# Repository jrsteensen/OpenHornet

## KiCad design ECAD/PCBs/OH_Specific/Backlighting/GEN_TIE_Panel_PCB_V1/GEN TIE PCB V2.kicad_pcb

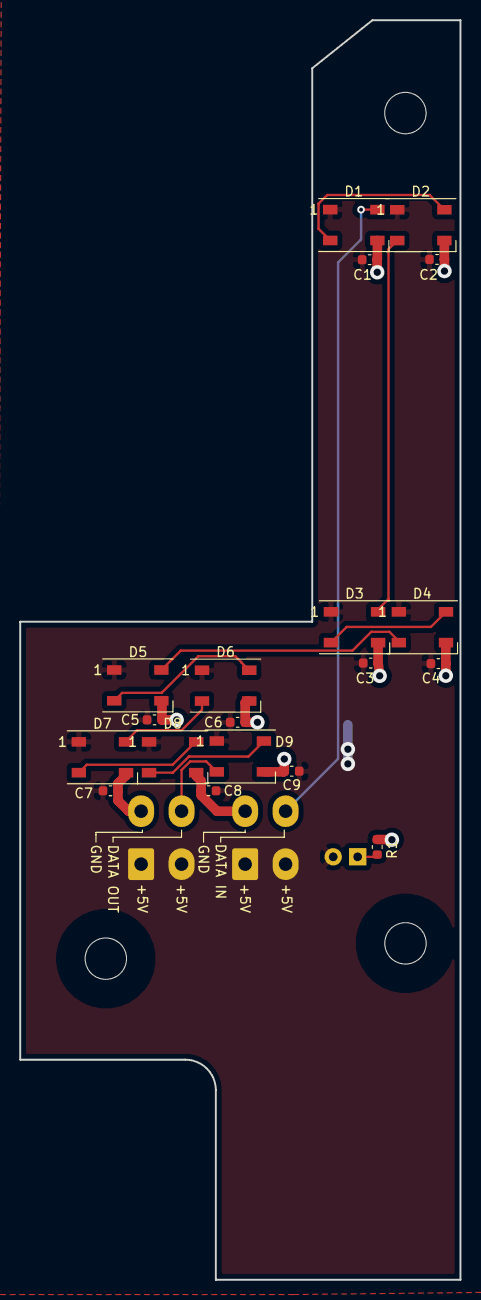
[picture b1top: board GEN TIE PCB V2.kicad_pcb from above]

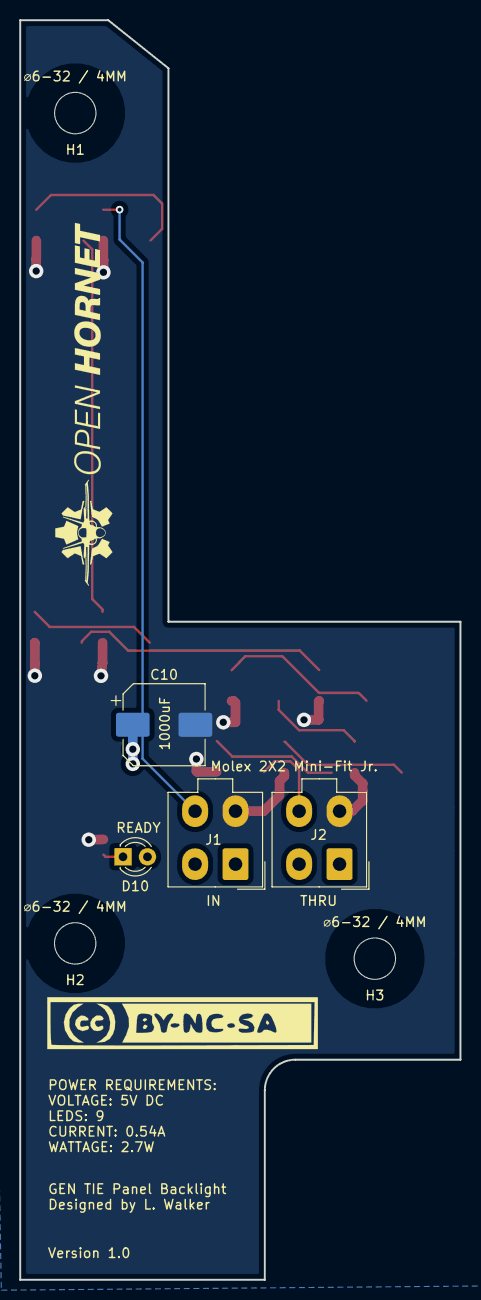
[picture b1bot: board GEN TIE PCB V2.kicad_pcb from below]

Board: 2 copper layers, 45.7 x 130.8 mm, 23 parts (4 on the bottom side), 13 nets.

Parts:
C1, C2, C3, C4, C5, C6, C7, C8, C9: C; C_0603_1608Metric
C10: C_Polarized; CP_Elec_8x10
D1, D2, D3, D4, D5, D6, D7, D8, D9: WS2812B; LED_WS2812B_PLCC4_5.0x5.0mm_P3.2mm
D10: LED; LED_D3.0mm
J1: IN; Molex_Mini-Fit_Jr_5566-04A_2x02_P4.20mm_Vertical
J2: THRU; Molex_Mini-Fit_Jr_5566-04A_2x02_P4.20mm_Vertical
R1: R; R_0603_1608Metric

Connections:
/DATAIN: D1.4, J1.4
/DATAOUT: D9.2, J2.4
/LED+5V: C1.1, C2.1, C3.1, C4.1, C5.1, C6.1, C7.1, C8.1, C9.1, C10.1, D1.1, D2.1, D3.1, D4.1, D5.1, D6.1, D7.1, D8.1, D9.1, D10.2, J1.1, J1.2, J2.1, J2.2
/LEDGND: C1.2, C2.2, C3.2, C4.2, C5.2, C6.2, C7.2, C8.2, C9.2, C10.2, D1.3, D2.3, D3.3, D4.3, D5.3, D6.3, D7.3, D8.3, D9.3, J1.3, J2.3, R1.2
unnamed: D1.2, D2.4
unnamed: D2.2, D3.4
unnamed: D3.2, D4.4
unnamed: D4.2, D5.4
unnamed: D5.2, D6.4
unnamed: D6.2, D7.4
unnamed: D7.2, D8.4
unnamed: D8.2, D9.4
unnamed: D10.1, R1.1

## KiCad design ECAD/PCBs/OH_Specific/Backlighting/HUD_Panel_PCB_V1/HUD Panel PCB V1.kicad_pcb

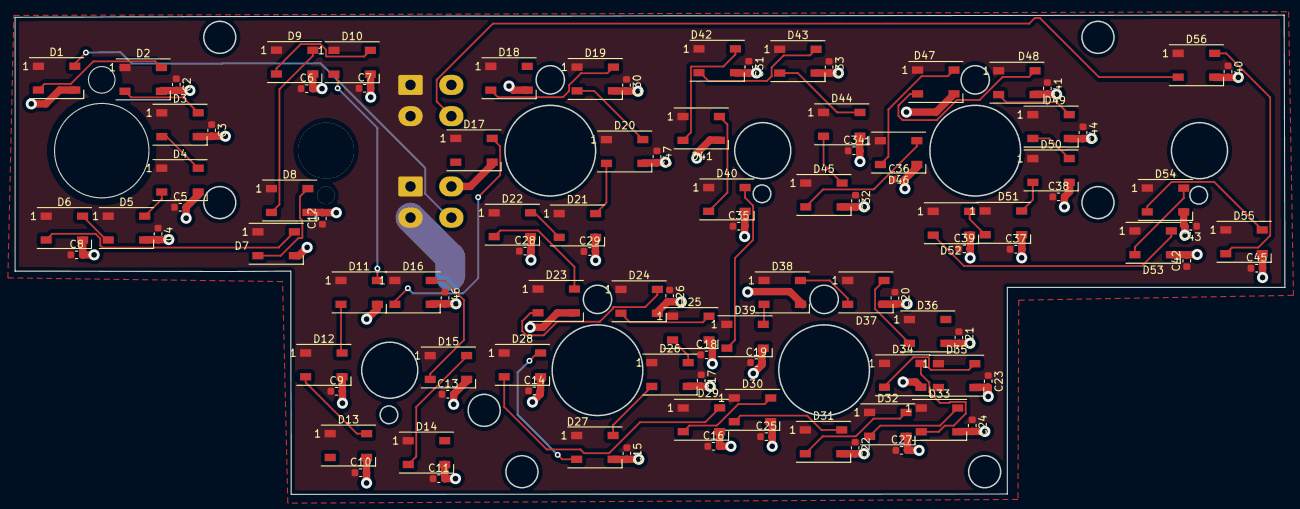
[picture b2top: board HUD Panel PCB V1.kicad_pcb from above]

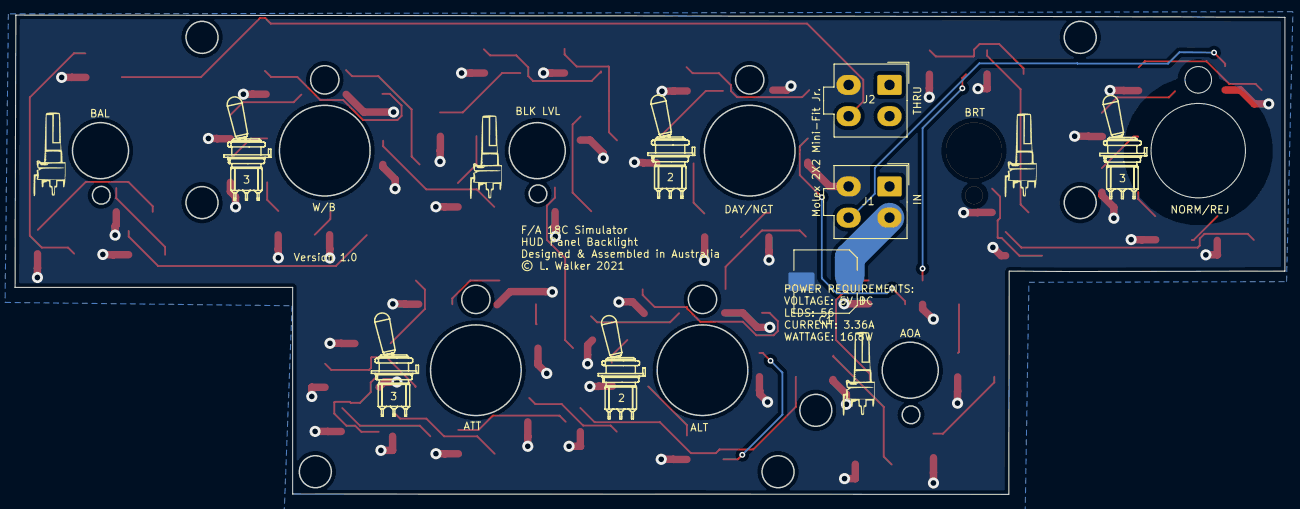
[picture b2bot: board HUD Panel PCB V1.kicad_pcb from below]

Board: 2 copper layers, 170.8 x 64.5 mm, 116 parts (7 on the bottom side), 56 nets.

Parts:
1: 100SPX_Toggle_13mm_x_18mm
1#2, 3, 5, 8, 9: LOGO; 100SpxToggle
2: BR10K_Pot_11mm_x_11mm
2#2, 4, 6, 7: LOGO; BR10KPot
C1: C_Polarized; CP_Elec_8x10
C2, C3, C4, C5, C6, C7, C8, C9, C10, C11, C12, C13, C14, C15, C16, C17, C18, C19, C20, C21, C22, C23, C24, C25, C26, C27, C28, C29, C30, C31, C32, C33, C34, C35, C36, C37, C38, C39, C40, C41, C42, C43, C44, C45, C46, C47: C; C_0603_1608Metric
D1, D2, D3, D4, D5, D6, D7, D8, D9, D10, D11, D12, D13, D14, D15, D16, D17, D18, D19, D20, D21, D22, D23, D24, D25, D26, D27, D28, D29, D30, D31, D32, D33, D34, D35, D36, D37, D38, D39, D40, D41, D42, D43, D44, D45, D46, D47, D48, D49, D50, D51, D52, D53, D54, D55, D56: WS2812B; LED_WS2812B_PLCC4_5.0x5.0mm_P3.2mm
J1, J2: Conn_01x04_Female; Molex_Mini-Fit_Jr_5566-04A_2x02_P4.20mm_Vertical

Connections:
/DATAIN: D1.4, J1.4
/DATAOUT: D56.2, J2.4
/LED+5V: C1.1, C2.1, C3.1, C4.1, C5.1, C6.1, C7.1, C8.1, C9.1, C10.1, C11.1, C12.1, C13.1, C14.1, C15.1, C16.1, C17.1, C18.1, C19.1, C20.1, C21.1, C22.1, C23.1, C24.1, C25.1, C26.1, C27.1, C28.1, C29.1, C30.1, C31.1, C32.1, C33.1, C34.1, C35.1, C36.1, C37.1, C38.1, C39.1, C40.1, C41.1, C42.1, C43.1, C44.1, C45.1, C46.1, C47.1, D1.1, D2.1, D3.1, D4.1, D5.1, D6.1, D7.1, D8.1, D9.1, D10.1, D11.1, D12.1, D13.1, D14.1, D15.1, D16.1, D17.1, D18.1, D19.1, D20.1, D21.1, D22.1, D23.1, D24.1, D25.1, D26.1, D27.1, D28.1, D29.1, D30.1, D31.1, D32.1, D33.1, D34.1, D35.1, D36.1, D37.1, D38.1, D39.1, D40.1, D41.1, D42.1, D43.1, D44.1, D45.1, D46.1, D47.1, D48.1, D49.1, D50.1, D51.1, D52.1, D53.1, D54.1, D55.1, D56.1, J1.1, J1.2, J2.1, J2.2
/LEDGND: C1.2, C2.2, C3.2, C4.2, C5.2, C6.2, C7.2, C8.2, C9.2, C10.2, C11.2, C12.2, C13.2, C14.2, C15.2, C16.2, C17.2, C18.2, C19.2, C20.2, C21.2, C22.2, C23.2, C24.2, C25.2, C26.2, C27.2, C28.2, C29.2, C30.2, C31.2, C32.2, C33.2, C34.2, C35.2, C36.2, C37.2, C38.2, C39.2, C40.2, C41.2, C42.2, C43.2, C44.2, C45.2, C46.2, C47.2, D1.3, D2.3, D3.3, D4.3, D5.3, D6.3, D7.3, D8.3, D9.3, D10.3, D11.3, D12.3, D13.3, D14.3, D15.3, D16.3, D17.3, D18.3, D19.3, D20.3, D21.3, D22.3, D23.3, D24.3, D25.3, D26.3, D27.3, D28.3, D29.3, D30.3, D31.3, D32.3, D33.3, D34.3, D35.3, D36.3, D37.3, D38.3, D39.3, D40.3, D41.3, D42.3, D43.3, D44.3, D45.3, D46.3, D47.3, D48.3, D49.3, D50.3, D51.3, D52.3, D53.3, D54.3, D55.3, D56.3, J1.3, J2.3
unnamed: D1.2, D2.4
unnamed: D2.2, D3.4
unnamed: D3.2, D4.4
unnamed: D4.2, D5.4
unnamed: D5.2, D6.4
unnamed: D6.2, D7.4
unnamed: D7.2, D8.4
unnamed: D8.2, D9.4
unnamed: D10.2, D11.4
unnamed: D9.2, D10.4
unnamed: D11.2, D12.4
unnamed: D12.2, D13.4
unnamed: D14.2, D15.4
unnamed: D15.2, D16.4
unnamed: D16.2, D17.4
unnamed: D18.2, D19.4
unnamed: D19.2, D20.4
unnamed: D20.2, D21.4
unnamed: D21.2, D22.4
unnamed: D22.2, D23.4
unnamed: D23.2, D24.4
unnamed: D24.2, D25.4
unnamed: D25.2, D26.4
unnamed: D26.2, D27.4
unnamed: D27.2, D28.4
unnamed: D28.2, D29.4
unnamed: D29.2, D30.4
unnamed: D30.2, D31.4
unnamed: D31.2, D32.4
unnamed: D32.2, D33.4
unnamed: D33.2, D34.4
unnamed: D34.2, D35.4
unnamed: D36.2, D37.4
unnamed: D37.2, D38.4
unnamed: D38.2, D39.4
unnamed: D39.2, D40.4
unnamed: D40.2, D41.4
unnamed: D41.2, D42.4
unnamed: D42.2, D43.4
unnamed: D43.2, D44.4
unnamed: D44.2, D45.4
unnamed: D45.2, D46.4
unnamed: D46.2, D47.4
unnamed: D47.2, D48.4
unnamed: D48.2, D49.4
unnamed: D49.2, D50.4
unnamed: D50.2, D51.4
unnamed: D51.2, D52.4
unnamed: D52.2, D53.4
unnamed: D53.2, D54.4
unnamed: D54.2, D55.4
unnamed: D55.2, D56.4

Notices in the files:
ECAD/PCBs/OH_Specific/Backlighting/HUD_Panel_PCB_V1/HUD Panel PCB V1.kicad_pcb:
© L. Walker 2021
